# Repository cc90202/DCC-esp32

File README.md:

```
                               .=########%%####%@@@*:
                               +############%%@@@@@@%
              %@%               %@@%%@%@%=-*@@+@@@@@:                  .
           :#%@@@%##%%%%%%%##%%%@@@@@#%+*-:+@@@@@@@@%%%%@@@@@@@%%%%@@@@@@########%%#=.:.
          .@@@@@@@@@@@@@@@@@@@@@%@@@@%%#%%%%@@@@@@@@@@@@@@@@@@@@@@@@%@@@@%%%%%%%%%%%-=+*+
          .@@@@@@@@@@@@@@@@@@@@@@@@@@@@@@@@@@@@@@@@@@@@@@@@@@@@@@@@@@@@@@@@@@@@@@@@@-=@@%.
       ---:@@@@@@@@@@@@@@@@@@@@@@@@@@@@@**@@@@@@@@@@@@@@@@@@@@@@@@@@@@@@@@@@@@@@@@@@--@@@.  -
       :  .%@@@@@@@@@@@@@@@@@@@@@@@@@@@%%#@@@@@@@@@@@@@@@@@@@@@@@@@@@@@@@@@@@@@@@@@@--@@@:  :
      ::  :%@@@@@@@@@@@@@@@@@@@@@@@@@@@@@@@@@@@@@@@@@@@@@@@@@@@@@@@@@@@@@@@@@@@@@@@@-::=@-  :-
      -==*:%@@@@@@@@@@@@@@@@@@@@@@%@@@@@@@@@@@@@@@@@@@@@@@@@@@@@@@@@@@@@@@@@@@@@%@@@=::-@+  -=
      -#+*#-:..........-:.........................................:-:::::---====*%%***:-@@#*#=
    @+-@@@@#@@@@@@@@@%@@@@@@@@@@@@@%%@@@@%%###%@@@@@@@@@@@@@@@*#@@@@@@@@@@@@@@@*@%@@@%:=@@@@@@@@.
    + -#@@@@@@@@@@@@@@@@@@@@@@@@@@@@@@@@@@@@@@@@@@@@@@@@@@@@@@@@@@@@@@@@@@@@@@@@@@@@@@-=@@@@@#=.
     -*%@@@#@@@@@@@@@@@@@@@@@@@@@@@@@@@@@@@@@@@@@@@@@@@@@@@@@@@@@@@@@@@@@@@@@@@@@@@@@@#*@@@@@@@@*.
   .=#@@@@@:.@@@@@@@@@@@@@@@@@@@@@@@@@@@@@@.            @@@@@@@@@@@@@@@%@@@@@@@@@@@@@@@      .*+
              ...%%@@@@@@-   ..*%#@@@@@%...              ..*##@@@@@*.:.. .##*@@@@@=....
#%#%##%%##%%#####%#%##%%%#%%###%#%#%##%%##%%#####%#%##%%##%%%####%#%##%%##%%#####%#%##%%##%%###%#%#%
###%#%%#%%%%%%#####%#%##%%%%%%#####%#%%#%%%%%#%####%#%##%%%%%%#####%#%##%%%%%%#####%#%%#%%%%%%#####%
+++++*++++++*++++++++*++++++*++++++++*++++++*++++++++*=+++++*++++++++*++++++*++++++++*++++++*+++++=+
```

# DCC-esp32

A complete DCC command station with RailCom, written in Rust for the ESP32, together with the design files of its printed board ([`hardware/pcb/`](hardware/pcb/)).

`no_std` Rust firmware for a DCC command station built on the ESP32-C6, using
`esp-hal`, Embassy async tasks and `esp-radio`. Together with its companion
hardware it drives up to 12 locomotives at once, controlled from the Roco Z21
app over a Z21-compatible UDP layer.

## What this software does

The track waveform comes out of the RMT peripheral, with packet swaps handled
inside the interrupt while the preamble is still playing. That keeps the signal
free of inter-packet gaps and costs under 0.4% of the CPU, which is what makes
12 simultaneous decoders possible without the signal degrading.

Above that sit the NMRA packet encoder for both locomotive control and service
mode, a scheduler that keeps every active decoder refreshed with its speed,
direction and function state, emergency stop and fault handling, and the
Z21-compatible network layer the app talks to.

The station also listens to what the decoders answer. It opens the RailCom
cutout in the waveform, captures the reply with a comparator front end and a
UART, and uses it to recognise which locomotives are on the track and to read
and write their CVs while they run.

WiFi credentials are configured at runtime from a setup page the board serves
itself, so nothing is baked in at build time. Protocol, encoder and scheduler
logic is pure and covered by host-side tests; the rest runs on the target.

The firmware is updated over WiFi by uploading a signed file from the browser.
If the new version does not work, the station goes back to the previous one
on its own.

## Hardware documentation

Read this before wiring or powering anything:

- [Command-station board](hardware/pcb/) — KiCad project and fabrication files of the printed board (rev B)
- [Breadboard wiring](docs/hardware/wiring.md) — what is connected to what, and why
- [Components inventory](docs/hardware/components-inventory.md) — mounted, in the drawer, left the design, to buy

The bench circuit is built around a Pololu DRV8874 carrier (#4035) driving the
two rails, with the RailCom cutout obtained by braking the bridge: two AND
gates and two inverters combine the waveform with a run signal so that both
bridge inputs rise together during the cutout. The decoder's answer is picked
up as a few tens of millivolts across a sense resistor in series with each
rail, squared up by an LM339 comparator and read by a serial port on the
board.

The firmware drives the DCC signal path and the control logic, but safe operation depends on the
external hardware around it: the power stage, the protection circuitry, and how the signals are
routed. Those documents describe one specific breadboard, not a general recipe, so do not wire a
track from this README alone.

## Getting started

1. Check with `espflash board-info` (espflash **4.3.0**) that the board has
   8 MB of flash. Then build the firmware and write it over USB:

   ```bash
   cargo run --release
   ```

   The first installation is done over USB. Later updates go over WiFi, as
   described in [Firmware updates over WiFi](#firmware-updates-over-wifi).

2. Configure WiFi from the ESP32 setup page.

   On first boot, or whenever no valid WiFi credentials are stored, the ESP32
   starts safe WiFi setup mode instead of the normal command-station runtime.
   Track output, DCC, RailCom, and Z21 services remain disabled during setup.

   Connect a phone or computer to:

   - AP SSID: `DCC-Setup-XXXX`, where `XXXX` is derived from the ESP32 MAC
     suffix
   - AP password: `dcc-setup`
   - Setup URL: `http://192.168.4.1`

   The setup page asks for the station WiFi SSID and password. After a valid
   save, the ESP32 sends the success page, reboots, and starts station mode
   using the stored credentials.

3. To re-enter setup mode later, hold the blue Resume button on GPIO21 for at
   least 10 seconds, then release it. The board reboots and starts the setup
   access point. This also works when the saved home WiFi network is absent.

   Short GPIO21 presses still perform Resume. A press below the 10 second setup
   threshold does not enter WiFi setup. The red Stop button on GPIO22 remains
   Stop/E-stop and is unchanged by WiFi provisioning.

4. Once station mode is connected, the OLED display shows the station's IP
   address.

5. In the Roco Z21 app, go to settings and enter that IP address as the command station.

6. Select the locomotive address and drive.

Programming on the main track works: the station reads and writes CVs over
RailCom while the locomotive is running, verified on the bench with ESU and
ZIMO decoders. Service-mode programming on a separate track is not available,
because the hardware it needs (track relay and acknowledgement detection) has
not been built yet.

## Build and flash

| Command | What it does |
|---------|--------------|
| `cargo build-esp` | Debug build for the ESP32-C6 |
| `cargo build-esp-release` | Release build (LTO, size-optimized) |
| `cargo check-esp` | Type-check for the ESP32-C6, without building an image |
| `cargo test-host` | Run the unit tests on the PC |
| `cargo run --release` | Write the firmware over USB and open the serial monitor |

The aliases are defined in `.cargo/config.toml`. Writing over USB erases the
update history and the previous version kept in memory.

## Firmware updates over WiFi

The firmware is updated over WiFi, without a USB cable. The new firmware
comes in a signed file with the `.dccfw` extension.

Download the `.dccfw` file to a folder on the PC. Turn the track off from
Z21. Open `http://<station-address>/update` in the browser; the station
address is shown on the display. Upload the file from the web page.

Before writing the file to memory, the station checks its signature, hash,
chip, flash layout and project name. It also checks that the file's version
is newer than the installed one and has not been rejected before. If a check
fails, the station refuses the file and the page explains why. If every check
passes, the station writes the new firmware to a partition of the ESP32.

The station then runs the new firmware on trial for one minute. During the
trial the two LEDs alternate, the display counts down the seconds left, the
track stays off and Z21 cannot turn it on. If the new firmware was installed
correctly, the station confirms the new version and the display asks to turn
the track on from Z21. The update is then complete.

If during the trial the new firmware hangs, restarts on its own or fails a
check, the station goes back to the previous version. The new version is
marked as rejected and the station will not accept it again. If instead the
trial is cut short by a power loss, the new version is not rejected and can
be uploaded again.

## Commit conventions

Commit messages follow Conventional Commits and are validated with `cocogitto`.

- Format: `type(scope)!: short imperative summary`
- Reference: [CONTRIBUTING.md](CONTRIBUTING.md)
- Local check: `cog check origin/main..HEAD`
- Local hook install: `cog install-hook`

## Project layout

- `src/bin/main.rs`: firmware entrypoint
- `src/boot.rs` and `src/boot/`: composition root, hardware setup, readiness, and task spawning
- `src/application/`: framework-independent use cases, safety policies, and read projections
- `src/dcc/`: scheduling, the waveform driver and the CV/POM actors; re-exports the protocol types from `dcc-protocol`
- `src/net/`: WiFi, provisioning, UDP transport, and Z21 interface adapters
- `src/railcom.rs` and `src/railcom/`: RailCom capture, parsing, attribution, and runtime dispatch
- `src/fault_manager.rs` and `src/fault_manager/`: track-safety policy, power fence, and effect relay
- `src/track_*.rs`: physical output, authorization, and safety boundaries
- `src/ota/`: firmware side of the WiFi update: flash, watchdog, track interlock and display
- `crates/dcc-protocol/`: DCC packets, their pulse encoding and timing, and the RailCom and logon data, with no hardware access
- `crates/z21/`: pure Z21 wire protocol, independent of transport
- `crates/dcc-provisioning/`: WiFi provisioning with no hardware access: setup page parser, DHCP replies, stored credentials and the boot decision
- `crates/dcc-ota/`: update logic with no hardware access: journal, trial, rollback and status page data
- `crates/dcc-ota-format/`: signed package and firmware image formats
- `docs/specs/`: protocol and standards references
- `docs/hardware/`: the breadboard as it is wired today, inventory and assembly notes
- `hardware/pcb/`: the printed board, KiCad project and fabrication files

## Safety notes

- The firmware is written for the power stage and the protection circuits described in the hardware documentation. With different hardware its behaviour is not guaranteed.
- For protocol, power-stage, or GPIO wiring changes, re-check the hardware documentation before flashing.
- DCC track power can damage decoders or hardware if the power stage is wired incorrectly.

## TODO

- [ ] Service-mode programming on a separate track. The packet encoder already
      builds the verify and write packets; what is missing is hardware.
- [ ] Z21 multi-client support (multiple apps controlling the same station)
- [ ] 3D-printed box for the board
- [ ] LocoNet integration

## License

MIT

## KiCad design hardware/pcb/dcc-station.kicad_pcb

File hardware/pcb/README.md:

# DCC command-station board

The board of the DCC-esp32 command station: 100 x 120 mm, two layers, powered by an external 12–19 V adapter. A Waveshare ESP32-C6-Zero and a Pololu DRV8874 carrier plug into its sockets.

## Status

Rev B is the current design. It was built by JLCPCB and works on a 15 V bench supply on J9: power, ESP32, display, LEDs, Wi-Fi, DCC to the track and RailCom reads, and it starts with the display unplugged. Not tried yet: a reversed supply, the buttons, a 19 V supply and a short on the track.

Rev A (PR #41, commit ceebd3d) was built by JLCPCB and works on a 15 V bench supply: power, ESP32, display, LEDs, buttons, Wi-Fi, DCC to the track and RailCom reads. It carried a 230 V mains module on the board. Do not connect a rev A board to the mains: power it with 15 V on the module's output pins, as it was tested.

What rev B changes:

- no mains on the board; power comes from a certified adapter through a barrel jack;
- reverse-polarity protection and a transient suppressor on the input;
- the input voltage is divided down to GPIO0, for a firmware check of the supply (not written yet);
- a screw terminal for a bench supply;
- three panel connectors instead of one, each cable with its own ground;
- pull-up resistors on the display bus, so the bus is defined with the display unplugged.

The CPL already carries the rotation corrections for JLCPCB's footprints; one exported again from KiCad would not.

## Power

Use a regulated adapter of 12 to 19 V, at least 2.5 A, with a 5.5 x 2.5 mm plug, centre positive, double insulated (Class II, the square-in-a-square symbol). Choose the voltage by scale: the track gets the adapter voltage minus about 1 V under load (bridge, clamp diodes, fuse), so 12 V for N and 15 V for H0.

A 5.5 x 2.1 mm plug goes into the 2.5 mm jack but makes poor contact; use the right plug.

Never use a 24 V adapter, even though it has the same plug. Nothing on the board is damaged by it, but the decoders would get 23 V, and the firmware does not check the input voltage yet.

For bench work, a bench supply can be connected to the screw terminal J9 ("+" and "−" on the silkscreen) instead of the adapter. Never use both at once: a bench supply set above the adapter would push current into it.

USB and the adapter can be connected at the same time.

## Parts bought separately

- Waveshare ESP32-C6-Zero on J4 and J5, USB-C toward the bottom edge.
- Pololu DRV8874 carrier #4035 on J6 and J7, VM and VIN at the top.
- SSD1306 I2C display at 3.3 V.
- Two normally-open push buttons, resume and stop.
- Three JST XH cables for the lid, pin 1 at the square pad:
  - J3, DISPLAY, 4 ways: 1 ground, 2 3.3 V, 3 display data, 4 display clock. Keep the cable under 20 cm.
  - J10, RESUME, 2 ways: 1 ground, 2 button.
  - J11, STOP, 3 ways: 1 ground, 2 button, 3 not connected. The third way keeps the stop cable out of RESUME; label both ends of the resume cable, since a 2-way housing can still be pushed into STOP.
- The adapter described under "Power", and a box.

J12, on the bottom edge right of the sense resistors, is three ground pins for an oscilloscope probe's ground clip.

`fab/dcc-station.step` is the 3D model of the assembled board, for designing a box. The barrel jack J1 sits on the left edge, where the box needs a round opening for the plug; C1 is 16 mm tall.

## Editing

Open `dcc-station.kicad_pro` in KiCad 10. The symbol of Q1 (AO4407A) is in `symbols/dcc.kicad_sym`, the footprints of F1 and of the barrel jack J1 (pads from the XKB drawing) in `footprints/dcc.pretty`.

## Licence

CERN Open Hardware Licence v2, strongly reciprocal ([`LICENSE`](LICENSE)).

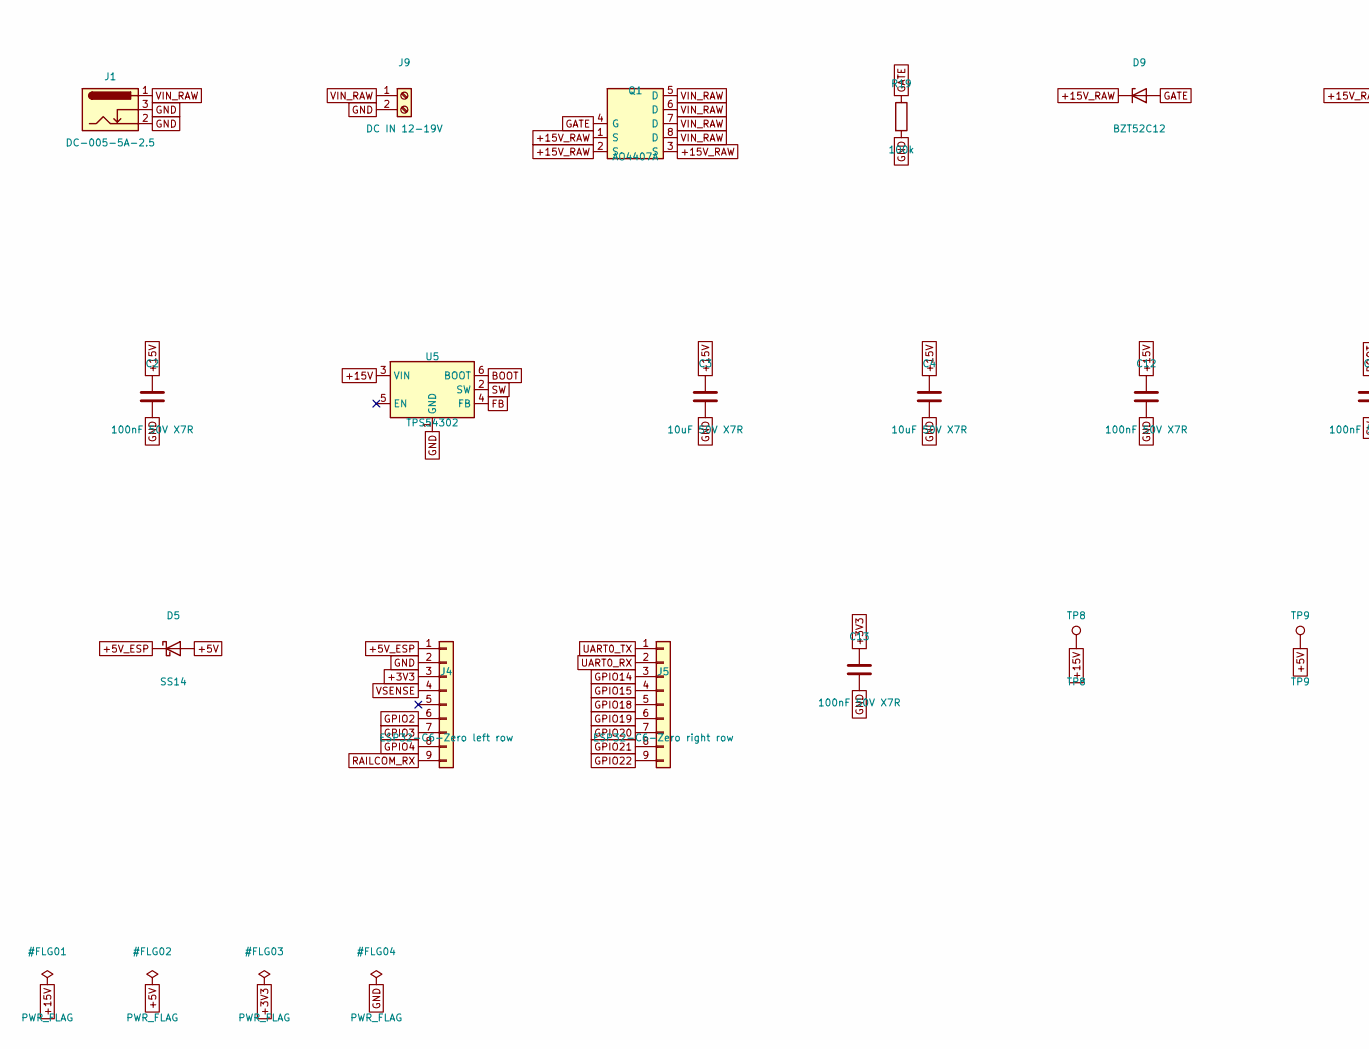
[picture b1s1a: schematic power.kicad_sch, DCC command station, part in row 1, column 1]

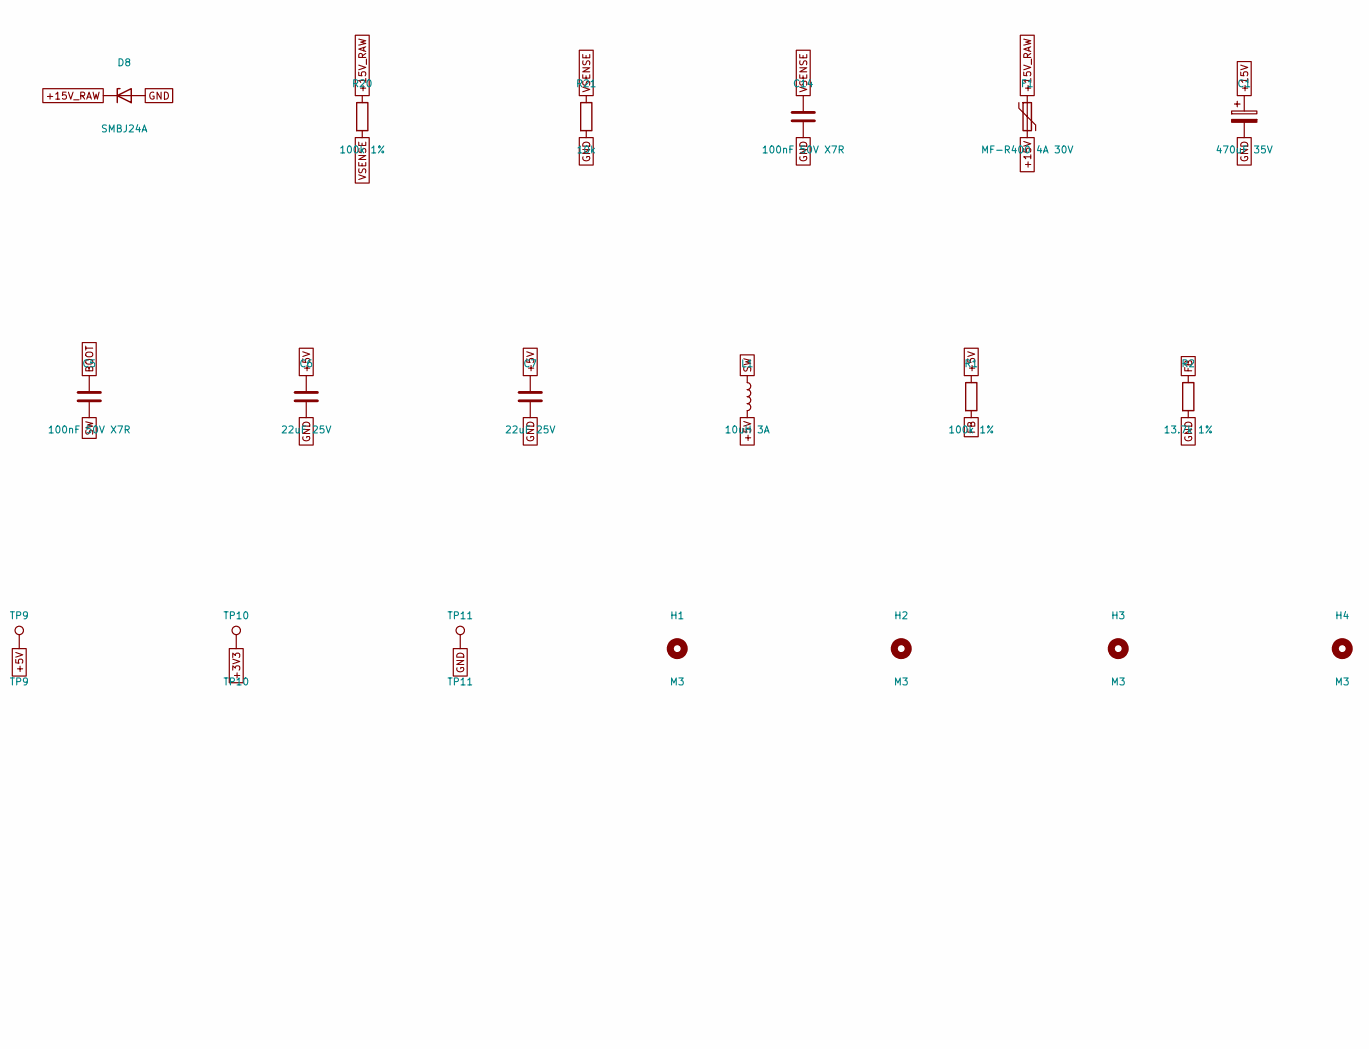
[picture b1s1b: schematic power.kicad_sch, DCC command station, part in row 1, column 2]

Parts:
C1: 470uF 35V; CP_Radial_D10.0mm_P5.00mm; LCSC C2835692
C2, C5, C12, C13, C14: 100nF 50V X7R; C_0805_2012Metric; LCSC C49678
C3, C4: 10uF 50V X7R; C_1210_3225Metric; LCSC C138687
C6, C7: 22uF 25V; C_1206_3216Metric; LCSC C12891
D5: SS14; D_SMA; LCSC C2480
D8: SMBJ24A; D_SMB; LCSC C135060
D9: BZT52C12; D_SOD-123; LCSC C727004
F1: MF-R400 4A 30V; Polyfuse_Radial_P5.08mm_W14.5mm; LCSC C208488
H1, H2, H3, H4: M3; MountingHole_3.2mm_M3
J1: DC-005-5A-2.5; BarrelJack_XKB_DC-005-5A; LCSC C381115
J4: ESP32-C6-Zero left row; PinSocket_1x09_P2.54mm_Vertical; LCSC C22438159
J5: ESP32-C6-Zero right row; PinSocket_1x09_P2.54mm_Vertical; LCSC C22438159
J9: DC IN 12-19V; TerminalBlock_Phoenix_MKDS-1,5-2_1x02_P5.00mm_Horizontal; LCSC C474950
L1: 10uH 3A; L_Bourns_SRN6045TA; LCSC C2046332
Q1: AO4407A; SOIC-8_3.9x4.9mm_P1.27mm; LCSC C2841482
R1, R20: 100k 1%; R_0805_2012Metric; LCSC C96346
R2: 13.7k 1%; R_0805_2012Metric; LCSC C17448
R19: 100k; R_0805_2012Metric; LCSC C96346
R21: 10k; R_0805_2012Metric; LCSC C17414
TP8: TP8; TestPoint_Pad_D1.5mm
TP9: TP9; TestPoint_Pad_D1.5mm
TP10: TP10; TestPoint_Pad_D1.5mm
TP11: TP11; TestPoint_Pad_D1.5mm
U5: TPS54302; TSOT-23-6; LCSC C311983

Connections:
+3V3: C13.1, J4.3, TP10.1; also elsewhere on the board
+5V: C6.1, C7.1, D5.2 (A), L1.2, R1.1, TP9.1; also elsewhere on the board
+5V_ESP: D5.1 (K), J4.1
+15V: C1.1, C2.1, C3.1, C4.1, C12.1, F1.2, TP8.1, U5.3 (VIN); also elsewhere on the board
+15V_RAW: D8.1 (K), D9.1 (K), F1.1, Q1.1 (S), Q1.2 (S), Q1.3 (S), R20.1
BOOT: C5.1, U5.6 (BOOT)
FB: R1.2, R2.1, U5.4 (FB)
GATE: D9.2 (A), Q1.4 (G), R19.1
GND: C1.2, C2.2, C3.2, C4.2, C6.2, C7.2, C12.2, C13.2, C14.2, D8.2 (A), J1.2, J1.3, J4.2, J9.2, R2.2, R19.2, R21.2, TP11.1, U5.1 (GND); also elsewhere on the board
GPIO2: J4.6; also elsewhere on the board
GPIO3: J4.7; also elsewhere on the board
GPIO4: J4.8; also elsewhere on the board
GPIO14: J5.3; also elsewhere on the board
GPIO15: J5.4; also elsewhere on the board
GPIO18: J5.5; also elsewhere on the board
GPIO19: J5.6; also elsewhere on the board
GPIO20: J5.7; also elsewhere on the board
GPIO21: J5.8; also elsewhere on the board
GPIO22: J5.9; also elsewhere on the board
RAILCOM_RX: J4.9; also elsewhere on the board
SW: C5.2, L1.1, U5.2 (SW)
UART0_RX: J5.2; also elsewhere on the board
UART0_TX: J5.1; also elsewhere on the board
VIN_RAW: J1.1, J9.1, Q1.5 (D), Q1.6 (D), Q1.7 (D), Q1.8 (D)
VSENSE: C14.1, J4.4, R20.2, R21.1

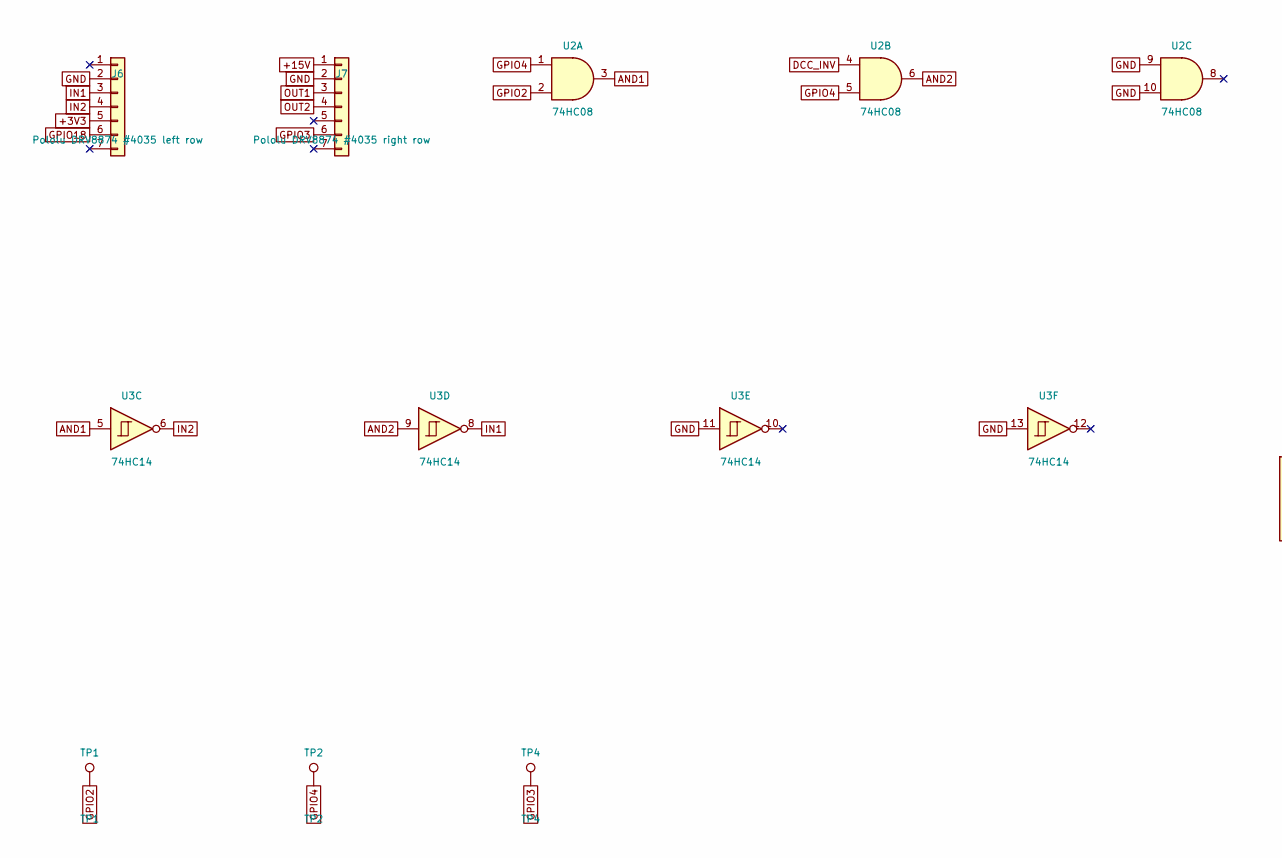
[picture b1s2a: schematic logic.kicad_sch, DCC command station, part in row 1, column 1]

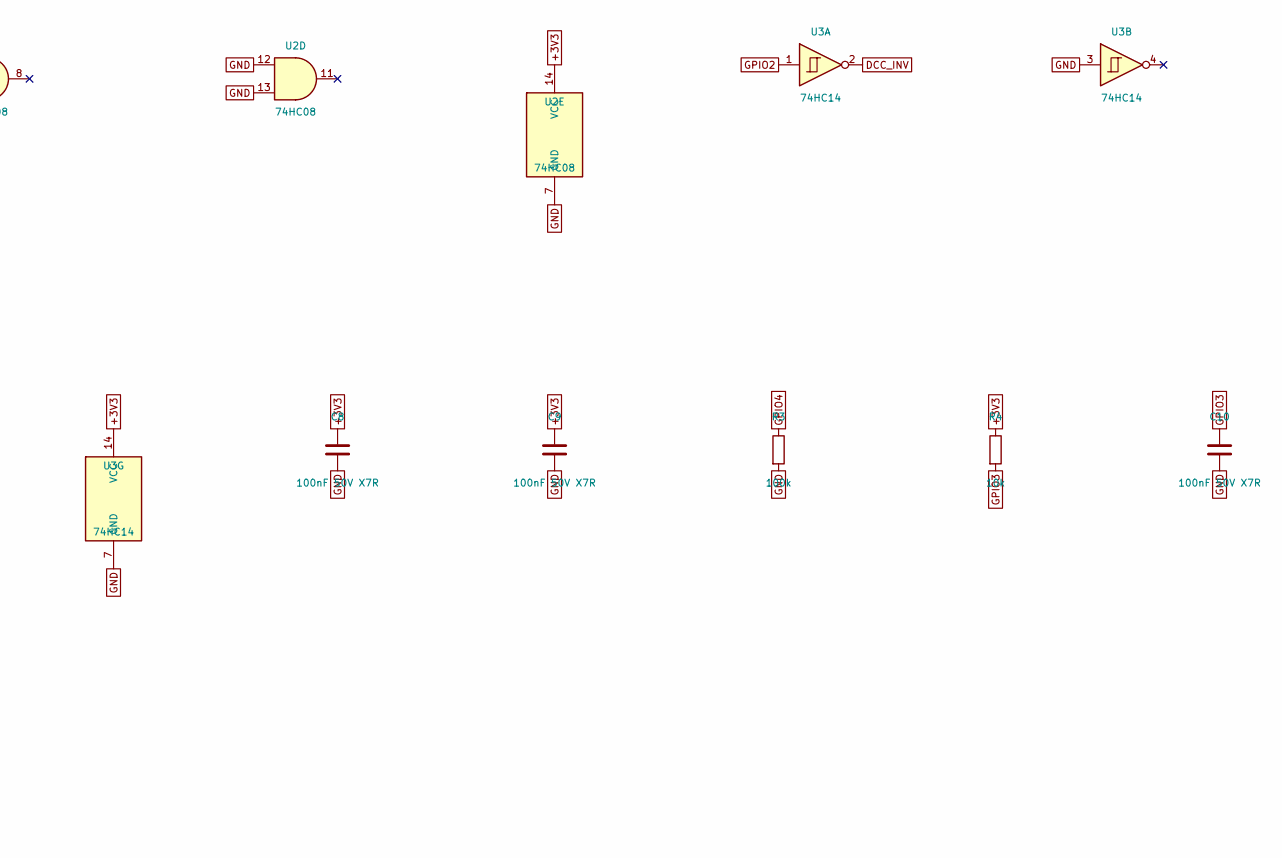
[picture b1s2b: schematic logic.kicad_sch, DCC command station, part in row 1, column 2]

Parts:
C8, C9, C10: 100nF 50V X7R; C_0805_2012Metric; LCSC C49678
J6: Pololu DRV8874 #4035 left row; PinSocket_1x07_P2.54mm_Vertical; LCSC C54876729
J7: Pololu DRV8874 #4035 right row; PinSocket_1x07_P2.54mm_Vertical; LCSC C54876729
R3: 100k; R_0805_2012Metric; LCSC C96346
R4: 10k; R_0805_2012Metric; LCSC C17414
TP1: TP1; TestPoint_Pad_D1.5mm
TP2: TP2; TestPoint_Pad_D1.5mm
TP4: TP4; TestPoint_Pad_D1.5mm
U2: 74HC08; SOIC-14_3.9x8.7mm_P1.27mm; LCSC C337768
U3: 74HC14; SOIC-14_3.9x8.7mm_P1.27mm; LCSC C6820

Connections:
+3V3: C8.1, C9.1, J6.5, R4.1, U2.14 (VCC), U3.14 (VCC); also elsewhere on the board
+15V: J7.1; also elsewhere on the board
AND1: U2.3, U3.5
AND2: U2.6, U3.9
DCC_INV: U2.4, U3.2
GND: C8.2, C9.2, C10.2, J6.2, J7.2, R3.2, U2.7 (GND), U2.9, U2.10, U2.12, U2.13, U3.3, U3.7 (GND), U3.11, U3.13; also elsewhere on the board
GPIO2: TP1.1, U2.2, U3.1; also elsewhere on the board
GPIO3: C10.1, J7.6, R4.2, TP4.1; also elsewhere on the board
GPIO4: R3.1, TP2.1, U2.1, U2.5; also elsewhere on the board
GPIO18: J6.6; also elsewhere on the board
IN1: J6.3, U3.8
IN2: J6.4, U3.6
OUT1: J7.3; also elsewhere on the board
OUT2: J7.4; also elsewhere on the board

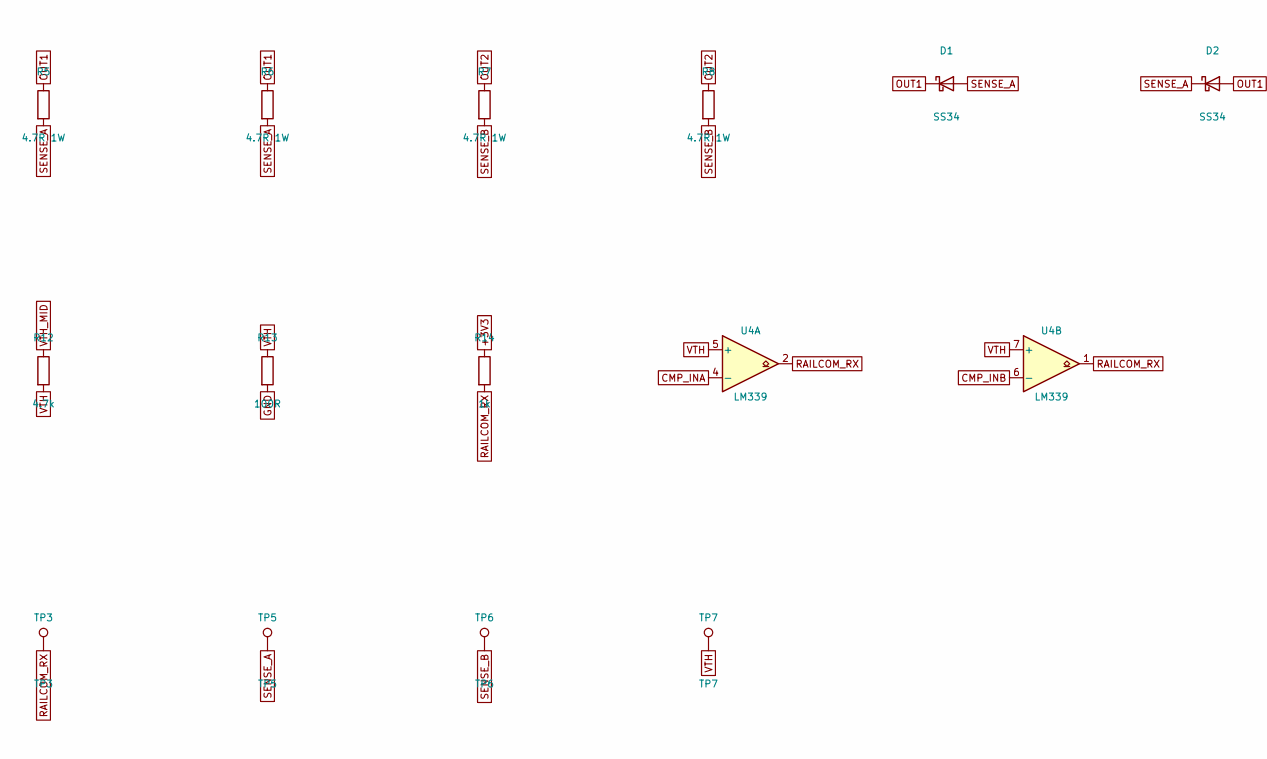
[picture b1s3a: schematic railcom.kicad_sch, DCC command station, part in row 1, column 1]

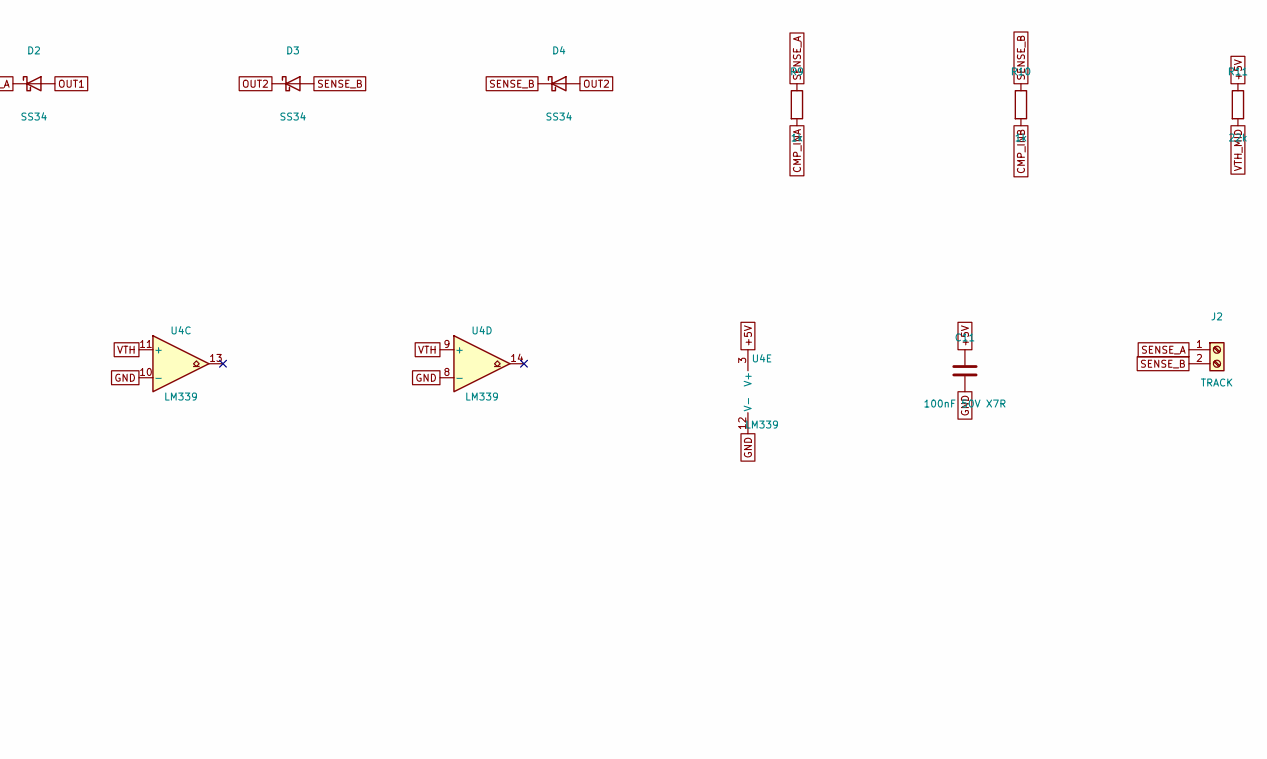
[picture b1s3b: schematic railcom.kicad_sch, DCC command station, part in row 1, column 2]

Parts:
C11: 100nF 50V X7R; C_0805_2012Metric; LCSC C49678
D1, D2, D3, D4: SS34; D_SMA; LCSC C8678
J2: TRACK; TerminalBlock_Phoenix_MKDS-1,5-2_1x02_P5.00mm_Horizontal; LCSC C474950
R5, R6, R7, R8: 4.7R 1W; R_2512_6332Metric; LCSC C25489
R9, R10, R14: 1k; R_0805_2012Metric; LCSC C17513
R11: 22k; R_0805_2012Metric; LCSC C17560
R12: 4.7k; R_0805_2012Metric; LCSC C17673
R13: 100R; R_0805_2012Metric; LCSC C17408
TP3: TP3; TestPoint_Pad_D1.5mm
TP5: TP5; TestPoint_Pad_D1.5mm
TP6: TP6; TestPoint_Pad_D1.5mm
TP7: TP7; TestPoint_Pad_D1.5mm
U4: LM339; SOIC-14_3.9x8.7mm_P1.27mm; LCSC C7948

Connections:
+3V3: R14.1; also elsewhere on the board
+5V: C11.1, R11.1, U4.3 (V+); also elsewhere on the board
CMP_INA: R9.2, U4.4 (-)
CMP_INB: R10.2, U4.6 (-)
GND: C11.2, R13.2, U4.8 (-), U4.10 (-), U4.12 (V-); also elsewhere on the board
OUT1: D1.1 (K), D2.2 (A), R5.1, R6.1; also elsewhere on the board
OUT2: D3.1 (K), D4.2 (A), R7.1, R8.1; also elsewhere on the board
RAILCOM_RX: R14.2, TP3.1, U4.1, U4.2; also elsewhere on the board
SENSE_A: D1.2 (A), D2.1 (K), J2.1, R5.2, R6.2, R9.1, TP5.1
SENSE_B: D3.2 (A), D4.1 (K), J2.2, R7.2, R8.2, R10.1, TP6.1
VTH: R12.2, R13.1, TP7.1, U4.5 (+), U4.7 (+), U4.9 (+), U4.11 (+)
VTH_MID: R11.2, R12.1

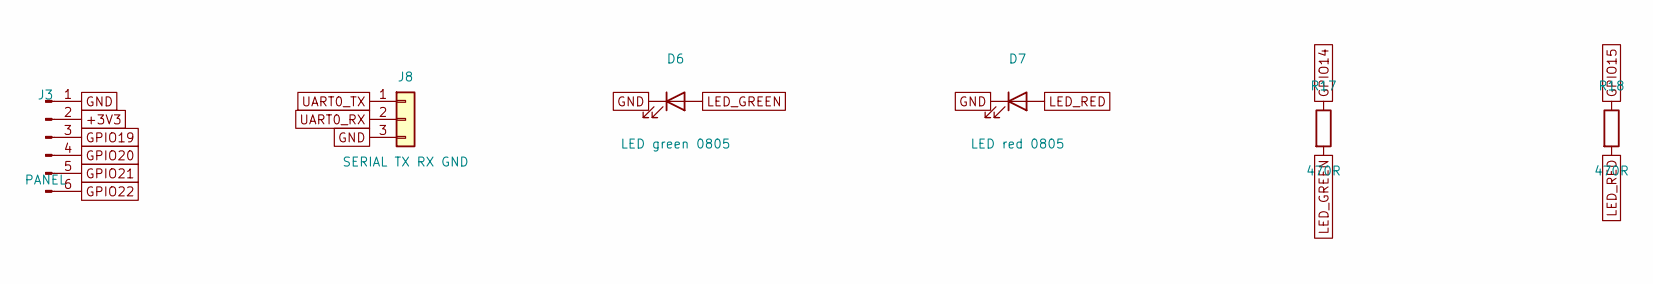
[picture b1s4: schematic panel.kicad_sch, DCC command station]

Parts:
D6: LED green 0805; LED_0805_2012Metric; LCSC C2297
D7: LED red 0805; LED_0805_2012Metric; LCSC C84256
J3: PANEL; JST_XH_B6B-XH-A_1x06_P2.50mm_Vertical; LCSC C144397
J8: SERIAL TX RX GND; PinHeader_1x03_P2.54mm_Vertical; LCSC C2937625
R17, R18: 470R; R_0805_2012Metric; LCSC C17710

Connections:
+3V3: J3.2; also elsewhere on the board
GND: D6.1 (K), D7.1 (K), J3.1, J8.3; also elsewhere on the board
GPIO14: R17.1; also elsewhere on the board
GPIO15: R18.1; also elsewhere on the board
GPIO19: J3.3; also elsewhere on the board
GPIO20: J3.4; also elsewhere on the board
LED_GREEN: D6.2 (A), R17.2
LED_RED: D7.2 (A), R18.2
UART0_RX: J8.2; also elsewhere on the board
UART0_TX: J8.1; also elsewhere on the board

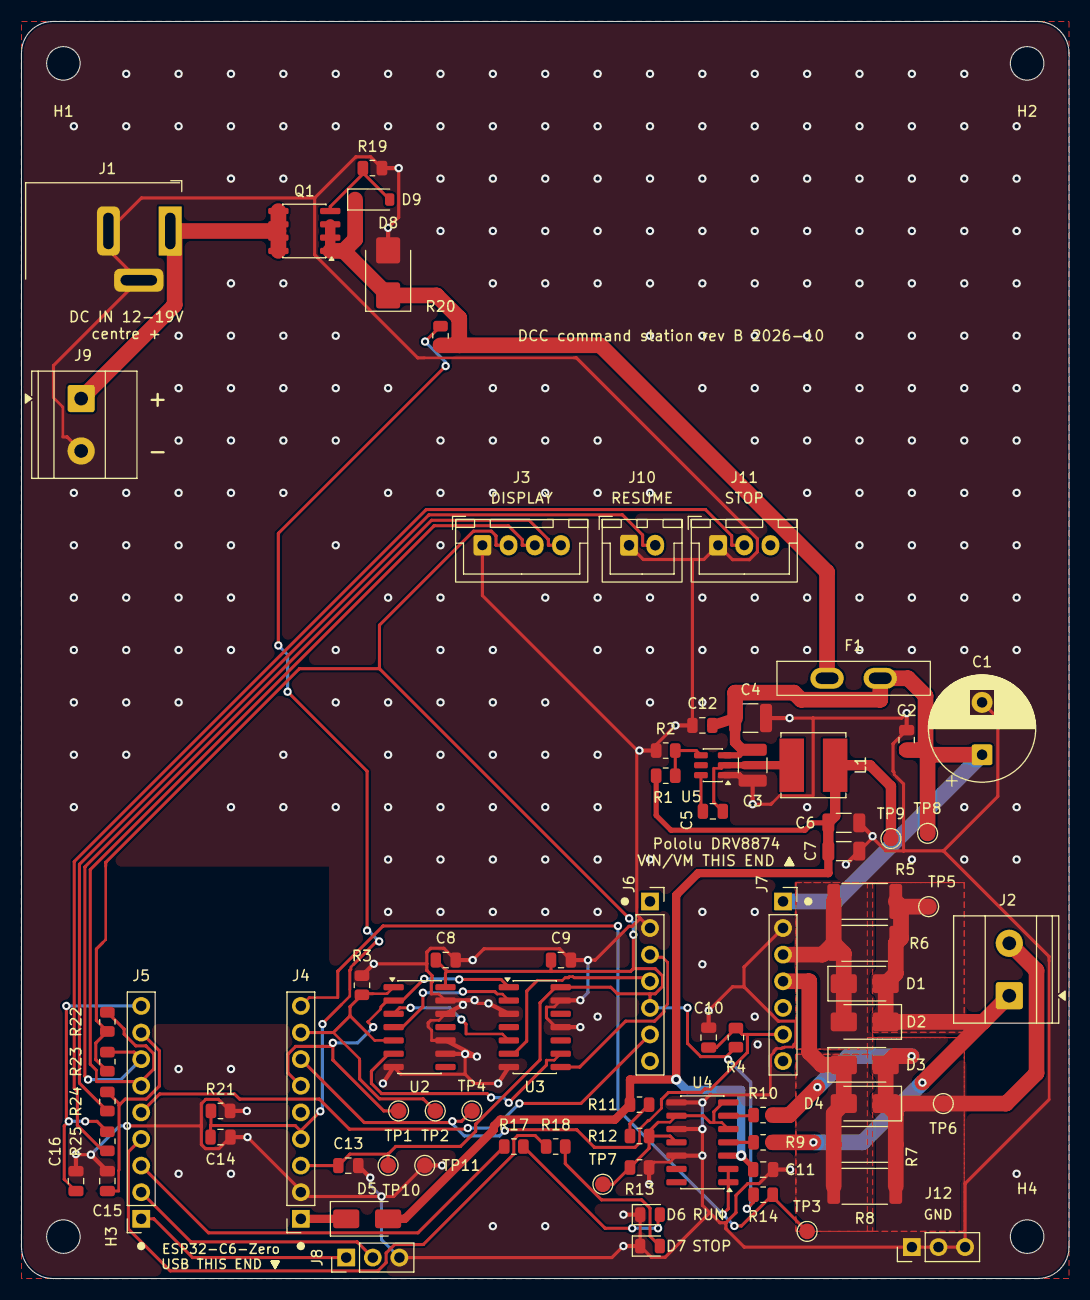
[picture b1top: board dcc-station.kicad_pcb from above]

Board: 2 copper layers, 100.0 x 120.0 mm, 82 parts (0 on the bottom side), 42 nets.

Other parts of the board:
C15, C16: 100nF 50V X7R; C_0805_2012Metric
J10: RESUME; JST_XH_B2B-XH-A_1x02_P2.50mm_Vertical
J11: STOP; JST_XH_B3B-XH-A_1x03_P2.50mm_Vertical
J12: GND SCOPE; PinHeader_1x03_P2.54mm_Vertical
R22, R23: 10k; R_0805_2012Metric
R24, R25: 1k; R_0805_2012Metric

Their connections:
+3V3: R22.1, R23.1; also elsewhere on the board
BTN_RESUME: J10.2, R24.1
BTN_STOP: J11.2, R25.1
GND: C15.2, C16.2, J10.1, J11.1, J12.1, J12.2, J12.3; also elsewhere on the board
GPIO19: R22.2; also elsewhere on the board
GPIO20: R23.2; also elsewhere on the board
GPIO21: C15.1, R24.2; also elsewhere on the board
GPIO22: C16.1, R25.2; also elsewhere on the board

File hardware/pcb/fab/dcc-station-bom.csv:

Comment,Designator,Footprint,LCSC Part #
470uF 25V,C1,CP_Radial_D10.0mm_P5.00mm,C338188
100nF 50V X7R,"C2,C5,C8,C9,C10,C11,C12,C13",C_0805_2012Metric,C49678
10uF 50V X7R,"C3,C4",C_1210_3225Metric,C138687
22uF 25V,"C6,C7",C_1206_3216Metric,C12891
SS34,"D1,D2,D3,D4",D_SMA,C8678
SS14,D5,D_SMA,C2480
LED green 0805,D6,LED_0805_2012Metric,C2297
LED red 0805,D7,LED_0805_2012Metric,C84256
MF-R400 4A 30V,F1,Polyfuse_Radial_P5.08mm_W14.5mm,C208488
MAINS L N 7.62mm,J1,TerminalBlock_7.62mm_1x02,C707824
TRACK,J2,"TerminalBlock_Phoenix_MKDS-1,5-2_1x02_P5.00mm_Horizontal",C474950
PANEL,J3,JST_XH_B6B-XH-A_1x06_P2.50mm_Vertical,C144397
ESP32-C6-Zero left row,J4,PinSocket_1x09_P2.54mm_Vertical,C22438159
ESP32-C6-Zero right row,J5,PinSocket_1x09_P2.54mm_Vertical,C22438159
Pololu DRV8874 #4035 left row,J6,PinSocket_1x07_P2.54mm_Vertical,C54876729
Pololu DRV8874 #4035 right row,J7,PinSocket_1x07_P2.54mm_Vertical,C54876729
SERIAL TX RX GND,J8,PinHeader_1x03_P2.54mm_Vertical,C2937625
10uH 3A,L1,L_Bourns_SRN6045TA,C2046332
IRM-45-15,PS1,Converter_ACDC_MeanWell_IRM-60-xx_THT,C5656527
100k 1%,R1,R_0805_2012Metric,C96346
13.7k 1%,R2,R_0805_2012Metric,C17448
100k,R3,R_0805_2012Metric,C96346
10k,R4,R_0805_2012Metric,C17414
4.7R 1W,"R5,R6,R7,R8",R_2512_6332Metric,C25489
1k,"R9,R10,R14",R_0805_2012Metric,C17513
22k,R11,R_0805_2012Metric,C17560
4.7k,R12,R_0805_2012Metric,C17673
100R,R13,R_0805_2012Metric,C17408
470R,"R17,R18",R_0805_2012Metric,C17710
74HC08,U2,SOIC-14_3.9x8.7mm_P1.27mm,C337768
74HC14,U3,SOIC-14_3.9x8.7mm_P1.27mm,C6820
LM339,U4,SOIC-14_3.9x8.7mm_P1.27mm,C7948
TPS54302,U5,TSOT-23-6,C311983

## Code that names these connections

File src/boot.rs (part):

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
struct DccCoreHardware {
    rmt: esp_hal::peripherals::RMT<'static>,
    dcc_pin: esp_hal::peripherals::GPIO2<'static>,
    timer: esp_hal::peripherals::TIMG1<'static>,
    track_enable_pin: esp_hal::peripherals::GPIO18<'static>,
    cutout_pin: esp_hal::peripherals::GPIO4<'static>,
    green_led_pin: esp_hal::peripherals::GPIO14<'static>,
    red_led_pin: esp_hal::peripherals::GPIO15<'static>,
}

fn spawn_display(
    spawner: &Spawner,
    i2c0: esp_hal::peripherals::I2C0<'static>,
    sda: esp_hal::peripherals::GPIO19<'static>,
    scl: esp_hal::peripherals::GPIO20<'static>,
) -> Result<(), BootError> {
    info!("boot: initializing I2C display bus");
    let i2c = match initialize_display_bus(i2c0, sda, scl) {
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}

async fn load_boot_wifi_decision(
    resume_pin: esp_hal::peripherals::GPIO21<'static>,
) -> Result<WifiBootDecision, BootError> {
    let mut resume_button = new_button_input(resume_pin);
    let boot_button_override = wait_for_boot_provisioning_override(&mut resume_button).await;
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
    verify_boot_packet_encoding()?;

    info!("boot: initializing RMT peripheral on GPIO2");
    initialize_dcc_rmt(rmt, dcc_pin)?;
    info!("boot: RMT initialized and DCC output mapped to GPIO2");
    DISPLAY_CHANNEL
        .send(DisplayEvent::BootProgress(BootStep::DccEngineReady))
        .await;
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    let command_receiver = scheduler_commands.receiver();
    info!("boot: scheduler command channel initialized");

    // The track sees no signal until the DCC waveform is stable. GPIO4 is
    // timer-driven for RailCom cutouts.
    let timg1 = TimerGroup::new(timer);
    let track_output = TrackOutput::new(track_enable_pin, cutout_pin, timg1.timer0);
    info!("boot: track SLEEP GPIO18 held LOW; RailCom cutout/run GPIO4 held inactive HIGH");

    spawn_critical(
        *spawner,
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struct SafetyRuntimeResources {
    partition_table_buffer: &'static mut [u8; PARTITION_TABLE_MAX_LEN],
    resume_button: Input<'static>,
    stop_pin: esp_hal::peripherals::GPIO22<'static>,
    short_detect_pin: esp_hal::peripherals::GPIO3<'static>,
}

async fn activate_safe_runtime(
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        ),
        CriticalTask::ResumeButton,
    )?;
    info!("boot: control button tasks spawned (GPIO22=stop, GPIO21=resume)");

    send_decoder_reset_sequence(sender).await;
    info!("boot: reset sequence complete (5 packets)");
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        ),
        CriticalTask::ShortDetector,
    )?;
    info!("boot: short detector task spawned (GPIO3 interrupt)");

    info!("boot: waiting for critical task readiness");
    wait_for_runtime_ready(BOOT_READY.receiver(), BOOT_FAILURE.receiver()).await?;
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
struct SetupHardware {
    wifi: esp_hal::peripherals::WIFI<'static>,
    green_led_pin: esp_hal::peripherals::GPIO14<'static>,
    red_led_pin: esp_hal::peripherals::GPIO15<'static>,
}

/// Runs the Wi-Fi setup access point; DCC, RailCom, Z21 and the track stay
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/// quietly instead: the recovery screen must stay, and a reset loop caused
/// by a boot error would hide it.
async fn wifi_decision_unless_recovery(
    resume_pin: esp_hal::peripherals::GPIO21<'static>,
) -> Result<Option<WifiBootDecision>, BootError> {
    match load_boot_wifi_decision(resume_pin).await {
        Ok(decision) => Ok(Some(decision)),
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    // Hold the physical bridge LOW before any flash access or boot decision,
    // until `TrackOutput` takes the pin over in `start_dcc_core`.
    let early_off = Output::new(
        peripherals.GPIO18.reborrow(),
        esp_hal::gpio::Level::Low,
        esp_hal::gpio::OutputConfig::default(),
    );
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    spawn_display(
        &spawner,
        peripherals.I2C0,
        peripherals.GPIO19,
        peripherals.GPIO20,
    )?;
    crate::ota::start(
        spawner,
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    SYSTEM_STATUS.send(SystemStatusEvent::BootStarted).await;
    NET_STATUS.send(SystemStatusEvent::BootStarted).await;

    let Some(wifi_decision) = wifi_decision_unless_recovery(peripherals.GPIO21).await? else {
        return Ok(());
    };
    let WifiBootDecision {
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                spawner,
                SetupHardware {
                    wifi: peripherals.WIFI,
                    green_led_pin: peripherals.GPIO14,
                    red_led_pin: peripherals.GPIO15,
                },
                partition_table_buffer,
            )
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    };

    // `Output` has no `Drop`, so the pin stays LOW after this line; the drop
    // keeps GPIO18 borrowed until here, so nothing else can claim it before
    // `TrackOutput` takes it over.
    #[expect(clippy::drop_non_drop, reason = "ends the borrow of GPIO18 here")]
    drop(early_off);
    let core = start_dcc_core(
        &spawner,
        DccCoreHardware {
            rmt: peripherals.RMT,
            dcc_pin: peripherals.GPIO2,
            timer: peripherals.TIMG1,
            track_enable_pin: peripherals.GPIO18,
            cutout_pin: peripherals.GPIO4,
            green_led_pin: peripherals.GPIO14,
            red_led_pin: peripherals.GPIO15,
        },
    )
    .await?;
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        SafetyRuntimeResources {
            partition_table_buffer,
            resume_button,
            stop_pin: peripherals.GPIO22,
            short_detect_pin: peripherals.GPIO3,
        },
    )
    .await?;
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
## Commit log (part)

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2026-03-27 Initial public release - DCC command station for ESP32-C6
2026-03-27 Initial public release — DCC command station for ESP32-C6
2026-03-27 fix(ci): add x86_64 host target to test workflow
2026-03-27 style: apply cargo fmt formatting fixes
2026-03-27 fix(ci): run tests only on ubuntu (test-host requires linux target)
2026-03-28 fix(display): make throbber timer resilient and faster
2026-03-30 feat(engine): ISR-driven RMT transmission, zero executor blocking
    Replace Embassy-task-based RMT engine with interrupt-driven architecture
    modelled after DCC-EX on ESP32. The RMT hardware loops continuously
    (TX_CONTI_MODE) and an ISR swaps the data portion in RMT RAM at each
    packet boundary, using the preamble playback (~2.3ms) as a timing buffer.
    New module rmt_driver.rs: init, ISR (CH_TX_LOOP via InfiniteWithInterrupt),
    shared buffer with ACK-based handshake preserving scheduler backpressure.
2026-03-30 perf(display): speed up throbber animation to 50ms interval
2026-04-02 feat(engine): ISR-driven RMT transmission, zero executor blocking
    Replace the executor-blocking DCC engine loop with an interrupt-driven
    RMT backend. The RMT peripheral now runs in continuous-loop mode and
    refills its buffer from a one-shot ISR, freeing the Embassy executor
    for other tasks. Pre-encoded idle packets are written directly to RMT
    RAM so the DCC signal never gaps.
    Key changes:
2026-04-02 style: align doc examples and display timing with develop
    - control_buttons.rs, status_led.rs: update doc examples to compilable form
    - display.rs: reduce throbber interval from 80ms to 50ms
    - net/mod.rs: add SAFETY comments on NVS linker stubs
